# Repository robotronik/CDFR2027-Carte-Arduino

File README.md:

# CDFR2027-Carte-Arduino
La carte Arduino Controle de moteur pour CDFR 2027

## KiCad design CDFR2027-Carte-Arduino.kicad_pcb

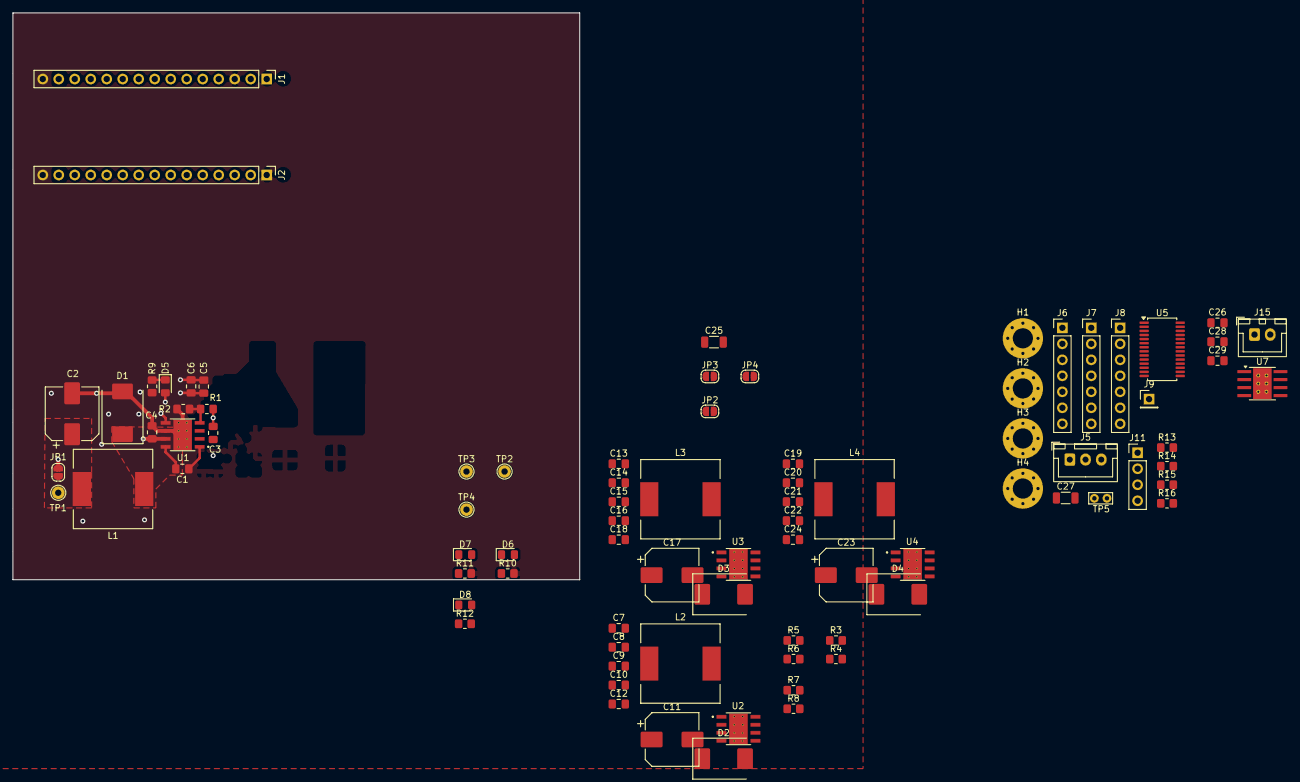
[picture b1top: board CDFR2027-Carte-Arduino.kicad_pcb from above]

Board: 4 copper layers, 90.0 x 90.0 mm, 85 parts (0 on the bottom side), 45 nets.

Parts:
C1, C3, C4, C9, C10, C12, C15, C16, C18, C21, C22, C24: 10nF; C_0805_2012Metric_Pad1.18x1.45mm_HandSolder
C2, C11, C17, C23: 330uF; CP_Elec_8x10
C5, C6, C7, C8, C13, C14, C19, C20, C26: 4.7uF; C_0805_2012Metric_Pad1.18x1.45mm_HandSolder
C25, C27: 22uF; C_1206_3216Metric
C28, C29: 100nF; C_0805_2012Metric_Pad1.18x1.45mm_HandSolder
D1, D2, D3, D4: B540C; D_SMC
D5, D6, D7, D8: LED; D_0805_2012Metric_Pad1.15x1.40mm_HandSolder
H1, H2, H3, H4: MountingHole_Pad; MountingHole_3.2mm_M3_Pad_Via
J1: Analog; PinHeader_1x15_P2.54mm_Vertical
J2: Digital; PinHeader_1x15_P2.54mm_Vertical
J5: Conn_01x03; JST_XH_B3B-XH-A_1x03_P2.50mm_Vertical
J6, J7, J8: Conn_01x07_Pin; PinHeader_1x07_P2.54mm_Vertical
J9: Conn_01x01_Pin; PinHeader_1x01_P2.54mm_Vertical
J11: Conn_01x04_Pin; PinHeader_1x04_P2.54mm_Vertical
J15: Conn_01x02; JST_XH_B2B-XH-A_1x02_P2.50mm_Vertical
JP1, JP2, JP3, JP4: SolderJumper_2_Open; SolderJumper-2_P1.3mm_Open_RoundedPad1.0x1.5mm
L1, L2, L3, L4: 15uH; L_12x12mm_H8mm
R1, R3, R5, R7, R16: 10k; R_0805_2012Metric_Pad1.20x1.40mm_HandSolder
R2, R4, R6, R8: 3.16k; R_0805_2012Metric_Pad1.20x1.40mm_HandSolder
R9, R10, R11, R12: 330R; R_0805_2012Metric_Pad1.20x1.40mm_HandSolder
R13, R14: 1k; R_0805_2012Metric_Pad1.20x1.40mm_HandSolder
R15: 100; R_0805_2012Metric_Pad1.20x1.40mm_HandSolder
TP1, TP2, TP3, TP4: TestPoint; TestPoint_THTPad_D2.0mm_Drill1.0mm
TP5: TestPoint; TestPoint_Bridge_Pitch2.0mm_Drill0.7mm
U1, U2, U3, U4: TPS5450DDAR; CONV_TPS5450DDAR
U5: PCA9685PW; TSSOP-28_4.4x9.7mm_P0.65mm
U7: DRV8870DDA; Texas_HTSOP-8-1EP_3.9x4.9mm_P1.27mm_EP2.95x4.9mm_Mask2.4x3.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

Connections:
+5V: C28.1, D5.2 (A), J1.12 (+5V), JP1.2 (B), R13.1, R14.1, R16.1, U5.1 (A0), U5.28 (VDD), U7.4 (VREF)
+BATT: C4.1, C5.1, C6.2, C7.2, C8.1, C9.1, C13.2, C14.1, C15.1, C19.2, C20.1, C21.1, C25.1, C26.1, C29.1, U1.7 (VIN), U2.7 (VIN), U3.7 (VIN), U4.7 (VIN), U7.5 (VM)
/5V DC1/5V_OUT: D6.2 (A), JP2.2 (B)
/5V DC2/5V_OUT: D7.2 (A), JP3.2 (B)
/5V DC3/5V_OUT: D8.2 (A), JP4.2 (B)
/I2C_CLK: J2.10 (D3), R13.2, U5.26 (SCL)
/I2C_DIO: J2.11 (D2), R14.2, U5.27 (SDA)
/LED_B: J11.4, U5.8 (PWM2)
/LED_G: J11.3, U5.7 (PWM1)
/LED_R: J11.2, U5.6 (PWM0)
/MASTER_I2C_CLK: J1.9 (SCL/D19), J5.1
/MASTER_I2C_DIO: J1.8 (SDA/D18), J5.2
/Output_Enable: R16.2, U5.23 (~OE)
/POW_EN: U2.5 (ENA), U3.5 (ENA), U4.5 (ENA)
/Servo1: J6.1, U5.9 (PWM3)
/Servo2: J6.2, U5.10 (PWM4)
/Servo3: J6.3, U5.11 (PWM5)
/Servo4: J6.4, U5.12 (PWM6)
/Servo5: J6.5, U5.13 (PWM7)
/Servo6: J6.6, U5.15 (PWM8)
/Servo7: J6.7, U5.16 (PWM9)
GND: C2.2, C3.2, C4.2, C5.2, C6.1, C7.1, C8.2, C9.2, C11.2, C12.2, C13.1, C14.2, C15.2, C17.2, C18.2, C19.1, C20.2, C21.2, C23.2, C24.2, C25.2, C26.2, C28.2, C29.2, D1.2 (A), D2.2 (A), D3.2 (A), D4.2 (A), H1.1 (1_1), H2.1 (1_1), H3.1 (1_1), H4.1 (1_1), J1.14 (GND), J2.12 (GND), J5.3, J8.1, J8.2, J8.3, J8.4, J8.5, J8.6, J8.7, J11.1, R2.2, R4.2, R6.2, R8.2, R9.2, R10.2, R11.2, R12.2, TP5.1 (1_1), U1.6 (GND), U1.9 (POWERPAD), U2.6 (GND), U2.9 (POWERPAD), U3.6 (GND), U3.9 (POWERPAD), U4.6 (GND), U4.9 (POWERPAD), U5.2 (A1), U5.3 (A2), U5.4 (A3), U5.5 (A4), U5.14 (VSS), U5.24 (A5), U5.25 (EXTCLK), U7.1 (GND), U7.7 (ISEN), U7.9 (GND)
unnamed: C1.2, D1.1 (K), L1.1, U1.8 (PH)
unnamed: C10.2, D2.1 (K), L2.1, U2.8 (PH)
unnamed: C16.2, D3.1 (K), L3.1, U3.8 (PH)
unnamed: C22.2, D4.1 (K), L4.1, U4.8 (PH)
unnamed: D5.1 (K), R9.1
unnamed: D6.1 (K), R10.1
unnamed: D7.1 (K), R11.1
unnamed: D8.1 (K), R12.1
unnamed: J7.1, J7.2, J7.3, J7.4, J7.5, J7.6, J7.7
unnamed: J15.1, U7.6 (OUT1)
unnamed: J15.2, U7.8 (OUT2)
unnamed: C2.1, C3.1, JP1.1 (A), L1.2, R1.1, TP1.1 (1_1)
unnamed: C11.1, C12.1, JP2.1 (A), L2.2, R3.1, TP2.1 (1_1)
unnamed: C17.1, C18.1, JP3.1 (A), L3.2, R5.1, TP3.1 (1_1)
unnamed: C23.1, C24.1, JP4.1 (A), L4.2, R7.1, TP4.1 (1_1)
unnamed: C1.1, U1.1 (BOOT)
unnamed: R1.2, R2.1, U1.4 (VSENSE)
unnamed: C10.1, U2.1 (BOOT)
unnamed: R3.2, R4.1, U2.4 (VSENSE)
unnamed: C16.1, U3.1 (BOOT)
unnamed: R5.2, R6.1, U3.4 (VSENSE)
unnamed: C22.1, U4.1 (BOOT)
unnamed: R7.2, R8.1, U4.4 (VSENSE)
